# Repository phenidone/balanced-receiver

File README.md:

# balanced-receiver

This is the PCB design for a simple, 4-channel balanced line-level receiver PCB with unbalanced outputs.
It is by no means a high performance (high CMRR from DC to daylight) design but it is good enough where
cable lengths are short and/or connect between units within a single rack.

The circuit uses one op-amp per channel. Attenuation is set via a voltage divider on the output,
which can be bridged for unity gain.

It has a first-order RC RF filter on the input, which results in non-optimal CMRR at HF.  While
a bootstrapped-capacitor arrangement would be "better", you end up with 4x as much silicon and
that's total overkill for those of us running short cables.

## Op-Amps

8-pin dual op-amps are required, in the standard footprint, e.g. LM833, TL072, etc.

If only two channels are required, you could leave U1 and its related R/C networks unpopulated.

## Power Supply

The receiver can be powered either from a regulated (about +/- 12V, depending on what your
chosen op-amps are rated for) or unregulated supply, e.g. the amplifier main filter caps.  Using
LM317 and LM337 regulators, the unregulated supply must be no greater than +/- 50V DC.

If you need many channels in a single box, you could populate the regulators on one board and chain
the other boards via the regulated-supply terminals.

Beware your ground routing and the relationship between grounds at: the power supply, the amplifier,
and this receiver board.  This receiver board should obtain its power and ground connections from
as close to the amp as possible, so as to avoid noise induced by power-supply currents in its
ground connections.

## Terminals

Use 0.2" screw terminals, Phoenix-style, for the power supply connection(s).

Use any suitable 0.1" pitch terminals for the analog inputs and outputs.  Screws are best, or
plug-in headers may suit in a low-vibration environment.

## License

This hardware design is (C) 2017 William Brodie-Tyrrell and is licensed under the CERN OHL; see cern_ohl_v_1_2.pdf

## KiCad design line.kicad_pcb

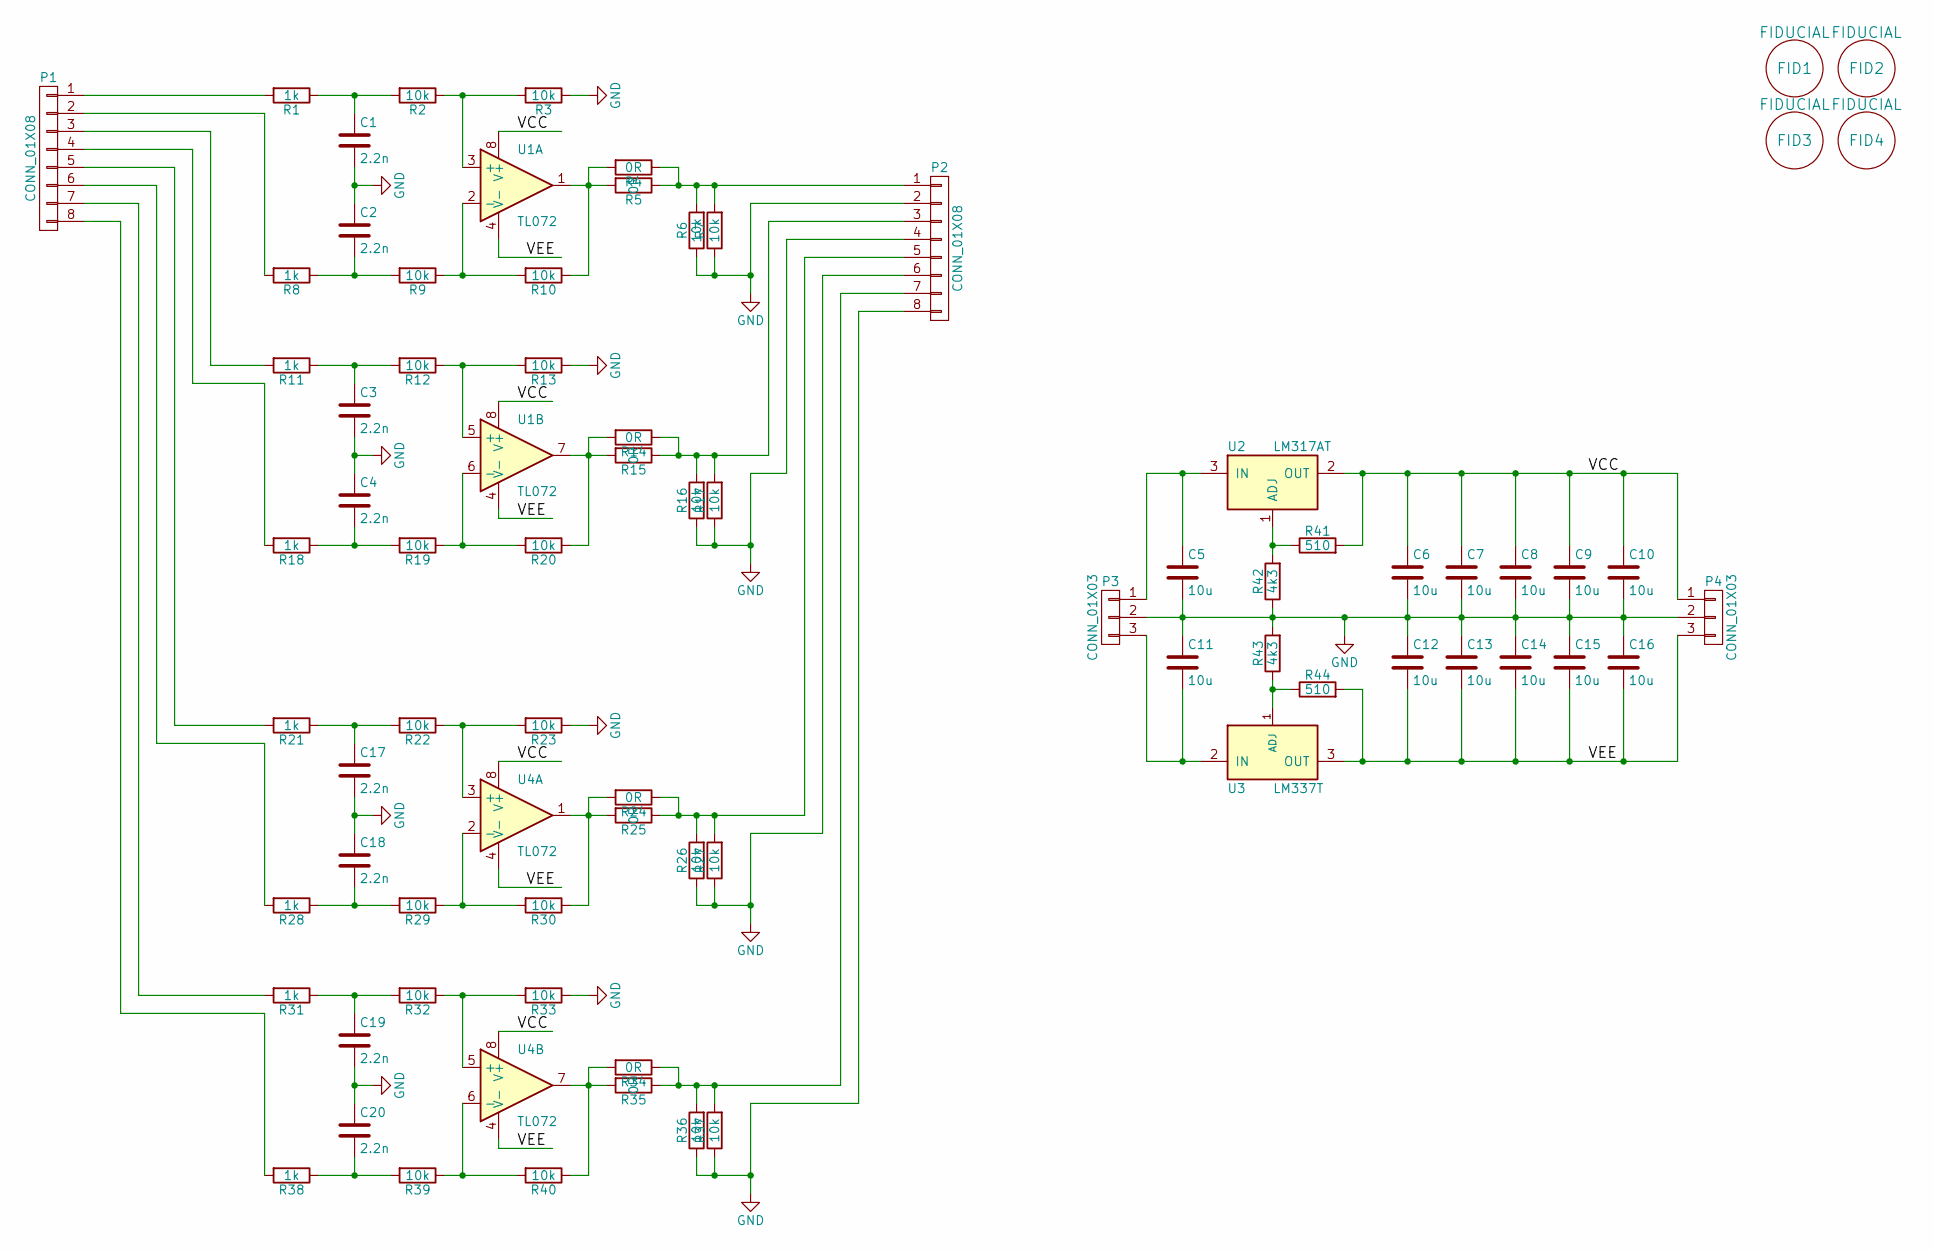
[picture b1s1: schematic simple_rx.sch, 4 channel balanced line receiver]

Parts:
C1, C2, C3, C4, C17, C18, C19, C20: 2.2n; C_0805
C5, C6, C7, C8, C9, C10, C11, C12, C13, C14, C15, C16: 10u; C_1206
FID1, FID2, FID3, FID4: FIDUCIAL; FID0.5
P1, P2: CONN_01X08; TerminalBlock_Pheonix_MPT-2.54mm_8pol
P3, P4: CONN_01X03; TerminalBlock_Pheonix_MKDS1.5-3pol
R1, R8, R11, R18, R21, R28, R31, R38: 1k; R_0805
R2, R3, R6, R7, R9, R10, R12, R13, R16, R17, R19, R20, R22, R23, R26, R27, R29, R30, R32, R33, R36, R37, R39, R40: 10k; R_0805
R4, R5, R14, R15, R24, R25, R34, R35: 0R; R_0805
R41, R44: 510; R_0805
R42, R43: 4k3; R_0805
U1, U4: TL072; DIP-8_W7.62mm_Socket
U2: LM317AT; TO-220
U3: LM337T; TO-220

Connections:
/VCC: C6.1, C7.1, C8.1, C9.1, C10.1, P4.1, R41.2, U1.8 (V+), U2.2 (OUT), U4.8 (V+)
/VEE: C12.2, C13.2, C14.2, C15.2, C16.2, P4.3, R44.2, U1.4 (V-), U3.3 (OUT), U4.4 (V-)
GND: C1.2, C2.1, C3.2, C4.1, C5.2, C6.2, C7.2, C8.2, C9.2, C10.2, C11.1, C12.1, C13.1, C14.1, C15.1, C16.1, C17.2, C18.1, C19.2, C20.1, P2.2, P2.4, P2.6, P2.8, P3.2, P4.2, R3.1, R6.1, R7.1, R13.1, R16.1, R17.1, R23.1, R26.1, R27.1, R33.1, R36.1, R37.1, R42.1, R43.2
unnamed: C1.1, R1.1, R2.2
unnamed: C2.2, R8.1, R9.2
unnamed: C3.1, R11.1, R12.2
unnamed: C4.2, R18.1, R19.2
unnamed: C5.1, P3.1, U2.3 (IN)
unnamed: C11.2, P3.3, U3.2 (IN)
unnamed: C17.1, R21.1, R22.2
unnamed: C18.2, R28.1, R29.2
unnamed: C19.1, R31.1, R32.2
unnamed: C20.2, R38.1, R39.2
unnamed: P1.1, R1.2
unnamed: P1.2, R8.2
unnamed: P1.3, R11.2
unnamed: P1.4, R18.2
unnamed: P1.5, R21.2
unnamed: P1.6, R28.2
unnamed: P1.7, R31.2
unnamed: P1.8, R38.2
unnamed: P2.1, R4.1, R5.1, R6.2, R7.2
unnamed: P2.3, R14.1, R15.1, R16.2, R17.2
unnamed: P2.5, R24.1, R25.1, R26.2, R27.2
unnamed: P2.7, R34.1, R35.1, R36.2, R37.2
unnamed: R2.1, R3.2, U1.3 (+)
unnamed: R4.2, R5.2, R10.1, U1.1
unnamed: R9.1, R10.2, U1.2 (-)
unnamed: R12.1, R13.2, U1.5 (+)
unnamed: R14.2, R15.2, R20.1, U1.7
unnamed: R19.1, R20.2, U1.6 (-)
unnamed: R22.1, R23.2, U4.3 (+)
unnamed: R24.2, R25.2, R30.1, U4.1
unnamed: R29.1, R30.2, U4.2 (-)
unnamed: R32.1, R33.2, U4.5 (+)
unnamed: R34.2, R35.2, R40.1, U4.7
unnamed: R39.1, R40.2, U4.6 (-)
unnamed: R41.1, R42.2, U2.1 (ADJ)
unnamed: R43.1, R44.1, U3.1 (ADJ)

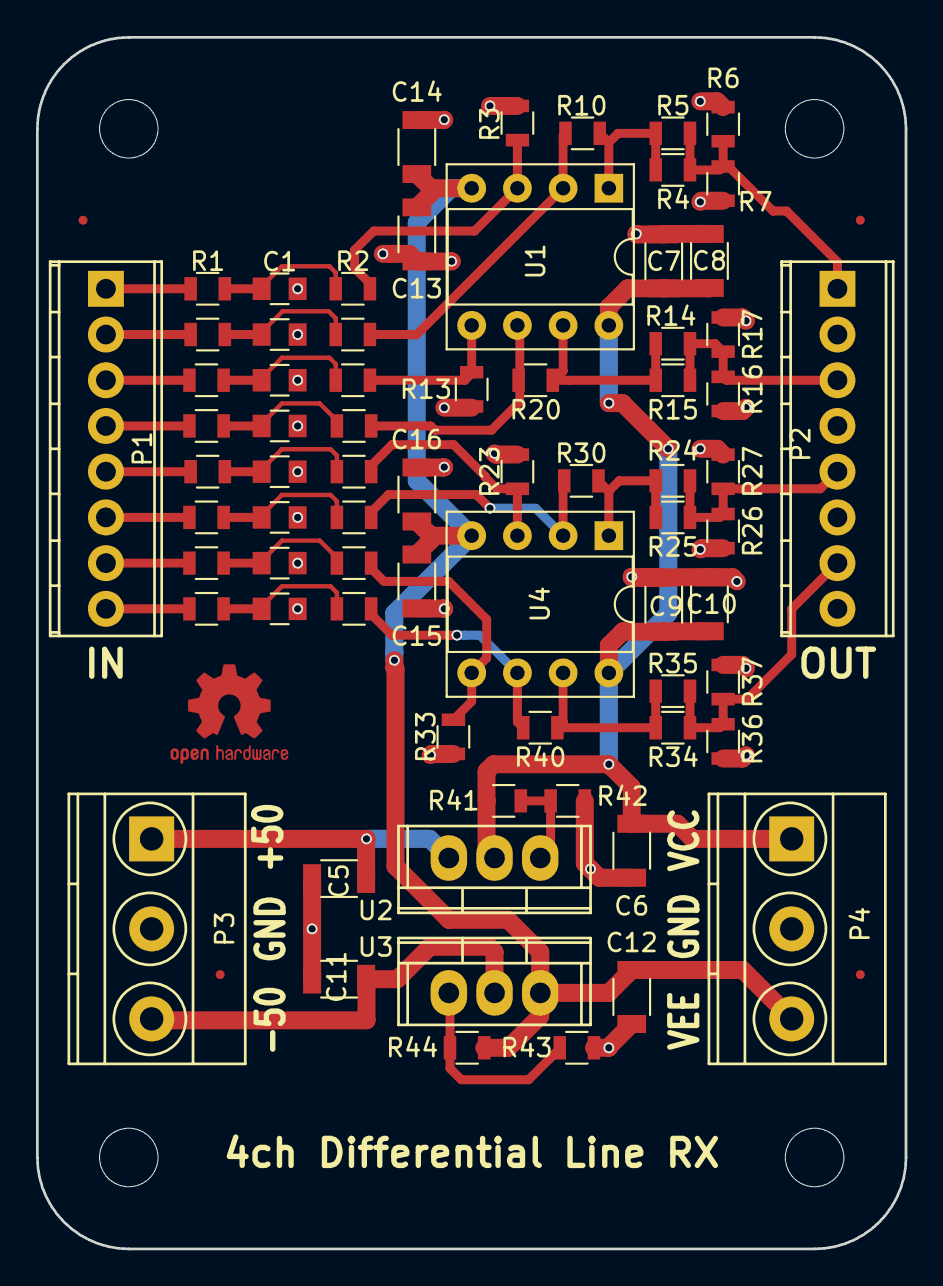
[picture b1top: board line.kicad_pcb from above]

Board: 2 copper layers, 48.3 x 67.3 mm, 76 parts (0 on the bottom side), 39 nets.

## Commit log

2017-10-21 drafted most of the simple line receiver
2017-10-21 added regulator layout
2017-10-22 line receiver PCB looks complete
2017-10-22 created schematic.pdf
2017-10-22 rounded corners, added gerbers
2017-10-22 added license
2017-10-24 converted power regulators to LM317/337 for higher voltage support
2017-10-24 cleaned up silkscreen
